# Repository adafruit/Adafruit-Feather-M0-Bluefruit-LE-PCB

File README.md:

## Adafruit Feather M0 Bluefruit LE PCB
<a href="http://www.adafruit.com/products/2995"><br/>
Click here to purchase one from the Adafruit shop</a>

This is the Adafruit Feather M0 Bluefruit LE - our take on an 'all-in-one' Arduino-compatible + Bluetooth Low Energy with built in USB and battery charging. It's an Adafruit Feather M0 with a BTLE module, ready to rock! We have other boards in the Feather family, check'em out here.

Bluetooth Low Energy is a hot, low-power, 2.4GHz spectrum wireless protocol. In particular, it's the only wireless protocol that you can use with iOS without needing special certification, and it's supported by all modern smart phones. This makes it excellent for use in portable projects that will make use of an iOS or Android phone or tablet. It also is supported in Mac OS X and Windows 8+.

At the Feather M0's heart is an ATSAMD21G18 ARM Cortex M0 processor, clocked at 48 MHz and at 3.3V logic, the same one used in the new Arduino Zero. This chip has a whopping 256K of FLASH (8x more than the Atmega328 or 32u4) and 32K of RAM (16x as much)! This chip comes with built in USB so it has USB-to-Serial program & debug capability built in with no need for an FTDI-like chip.

PCB files for the Adafruit Feather M0 Bluefruit LE PCB. The format is EagleCAD schematic and board layout
- https://www.adafruit.com/product/2995

### License

Adafruit invests time and resources providing this open source design, please support Adafruit and open-source hardware by purchasing products from [Adafruit](https://www.adafruit.com)!

All text above must be included in any redistribution

Designed by Limor Fried/Ladyada for Adafruit Industries.
Creative Commons Attribution/Share-Alike, all text above must be included in any redistribution. 
See license.txt for additional information.

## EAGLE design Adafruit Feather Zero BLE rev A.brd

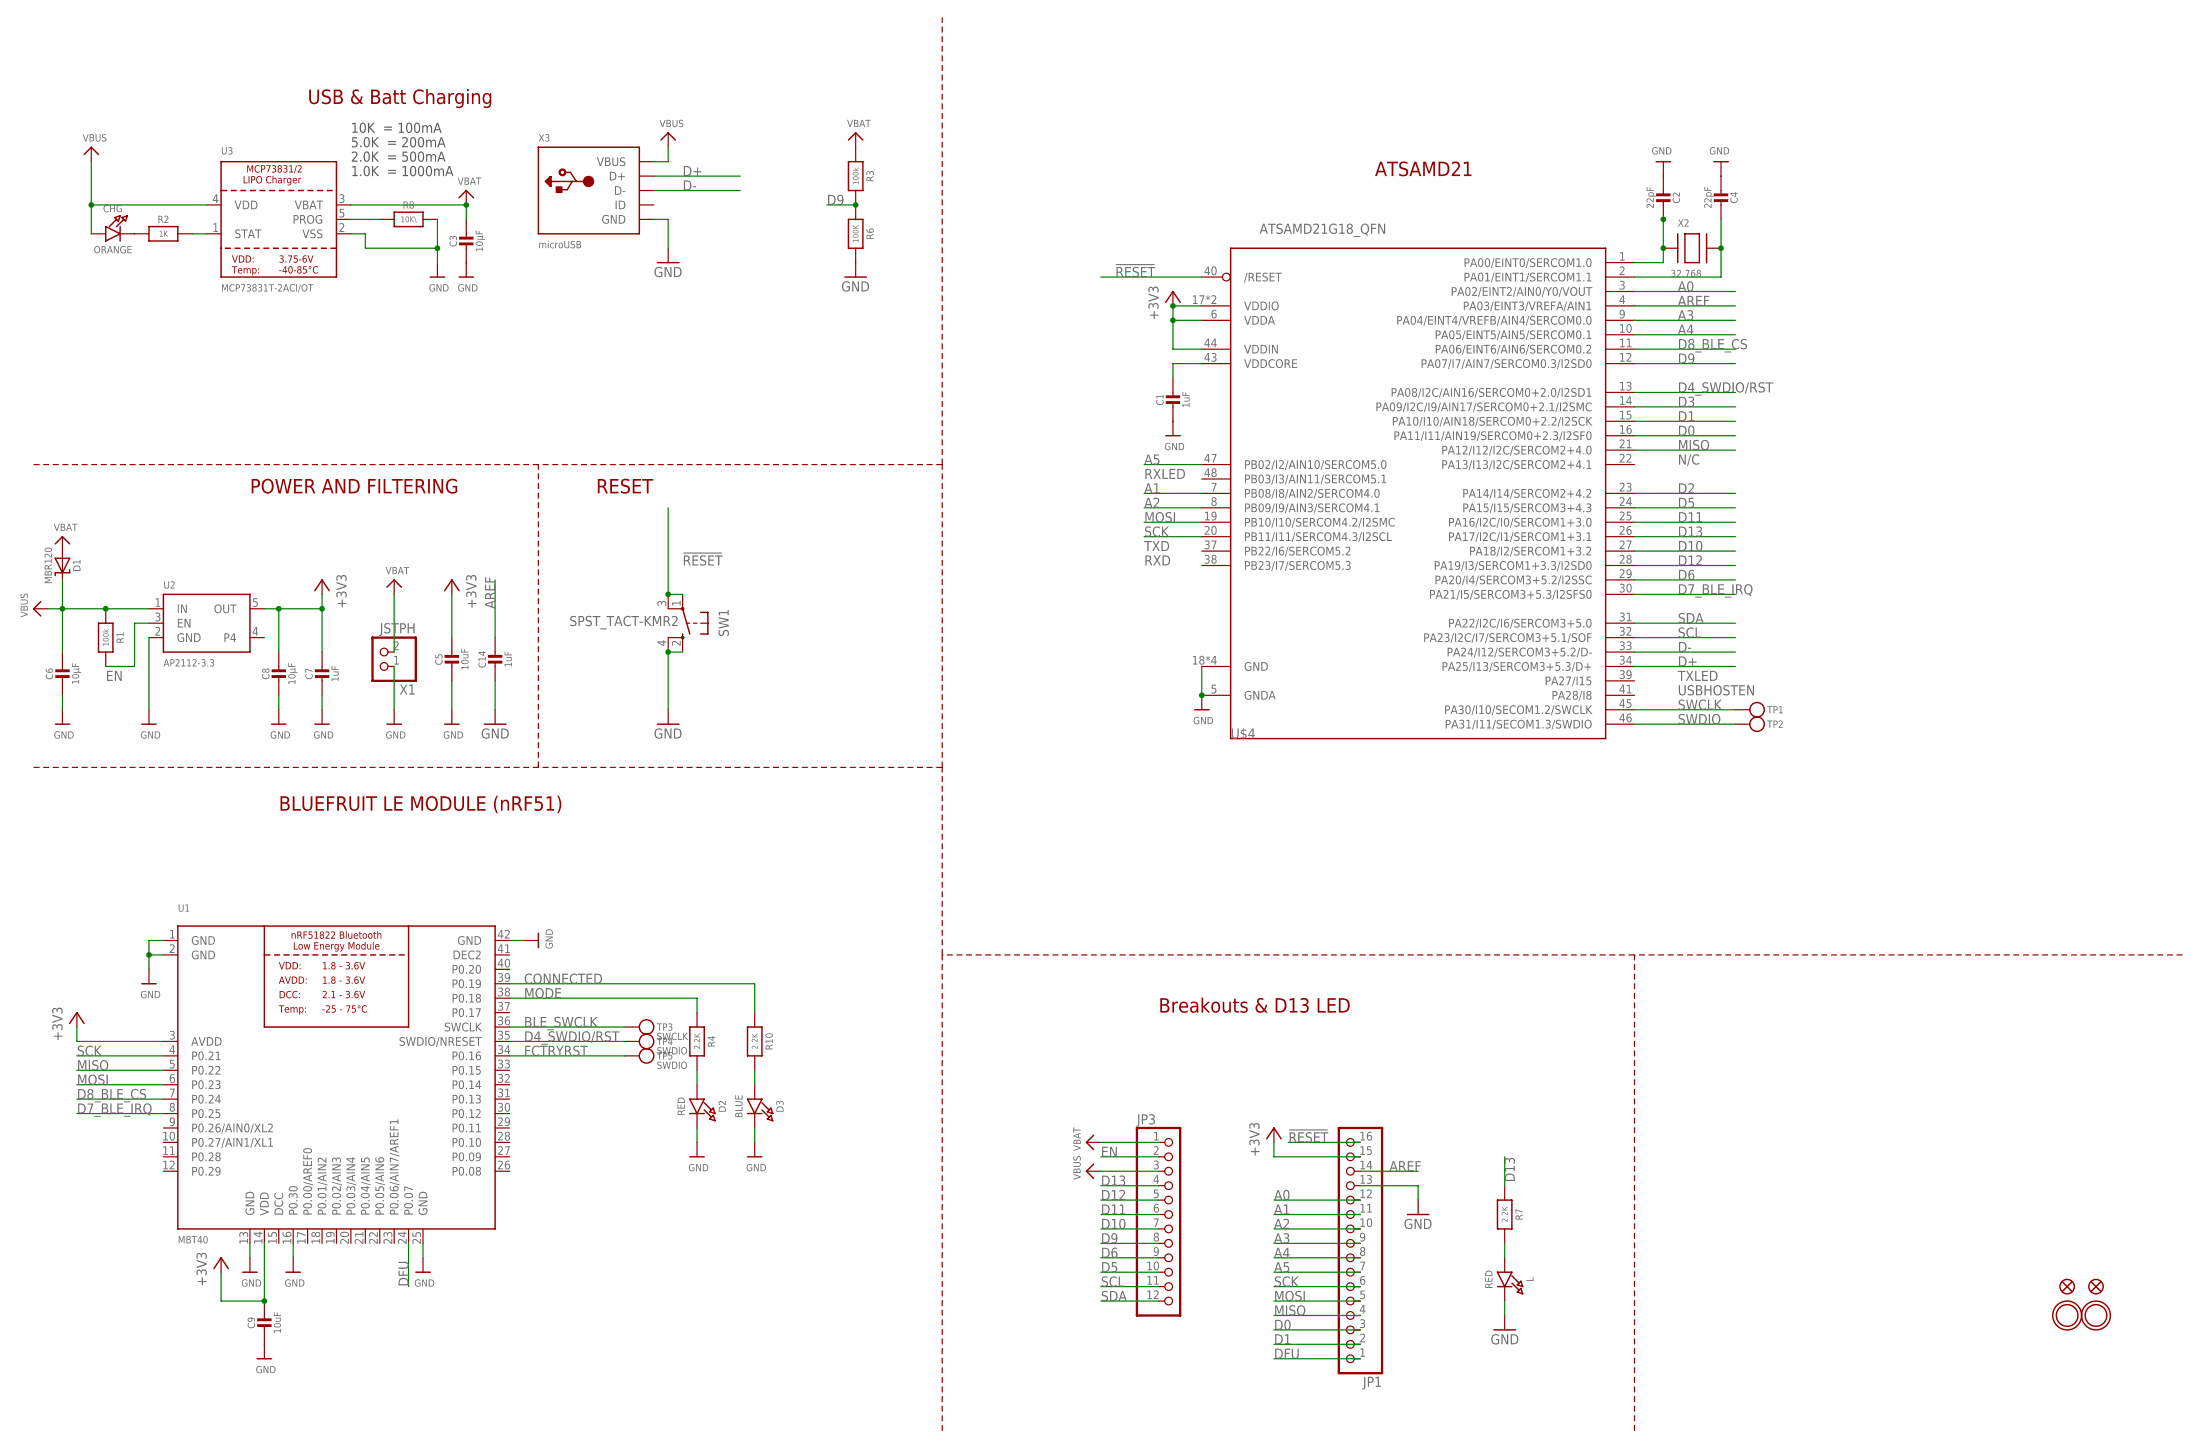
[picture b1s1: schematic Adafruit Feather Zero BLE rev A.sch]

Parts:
C1, C7, C14: 1uF; 0603-NO
C2, C4: 22pF; 0603-NO
C3, C6, C8: 10µF; 0805-NO
C5, C9: 10uF; 0805-NO
CHG: ORANGE; CHIPLED_0805_NOOUTLINE
D1: MBR120; SOD-123
D2: RED; CHIPLED_0805_NOOUTLINE
D3: BLUE; CHIPLED_0805_NOOUTLINE
JP1: HEADER-1X16ROUND; 1X16_ROUND
JP3: HEADER-1X12; 1X12_ROUND
L: RED; CHIPLED_0805_NOOUTLINE
R1, R3: 100k; 0603-NO
R2: 1K; 0603-NO
R4, R7, R10: 2.2K; 0603-NO
R6: 100K; 0603-NO
R8: 10K\; 0603-NO
SW1: SPST_TACT-KMR2; KMR2
TP1, TP2: TESTPOINTROUND1.5MM; TESTPOINT_ROUND_1.5MM
TP3: SWCLK; PAD-1.5X2.0
TP4, TP5: SWDIO; PAD-1.5X2.0
U1: MBT40; BLE_MODULE_RAYTAC_MDBT40
U2: AP2112-3.3; SOT23-5
U3: MCP73831T-2ACI/OT; SOT23-5
U$4: ATSAMD21G18_QFN; TQFN48_7MM
U$31, U$32: MOUNTINGHOLE2.5; MOUNTINGHOLE_2.5_PLATED
U$34, U$35: FIDUCIAL""; FIDUCIAL_1MM
X1: JSTPH; JSTPH2
X2: 32.768; XTAL3215
X3: microUSB; 4UCONN_20329_V2

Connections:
!RESET: JP1.16, SW1.1, SW1.3 (P1), U$4.40 (/RESET)
+3V3: C5.1, C7.1, C8.1, C9.1, JP1.15, U1.3 (AVDD), U1.14 (VDD), U2.5 (OUT), U$4.6 (VDDA), U$4.17 (VDDIO), U$4.36 (VDDIO), U$4.44 (VDDIN)
A0: JP1.12, U$4.3 (PA02/EINT2/AIN0/Y0/VOUT)
A1: JP1.11, U$4.7 (PB08/I8/AIN2/SERCOM4.0)
A2: JP1.10, U$4.8 (PB09/I9/AIN3/SERCOM4.1)
A3: JP1.9, U$4.9 (PA04/EINT4/VREFB/AIN4/SERCOM0.0)
A4: JP1.8, U$4.10 (PA05/EINT5/AIN5/SERCOM0.1)
A5: JP1.7, U$4.47 (PB02/I2/AIN10/SERCOM5.0)
AREF: C14.1, JP1.14, U$4.4 (PA03/EINT3/VREFA/AIN1)
BLE_SWCLK: TP3.P$1, U1.36 (SWCLK)
CONNECTED: R10.1, U1.39 (P0.19)
D0: JP1.3, U$4.16 (PA11/I11/AIN19/SERCOM0+2.3/I2SF0)
D1: JP1.2, U$4.15 (PA10/I10/AIN18/SERCOM0+2.2/I2SCK)
D2: U$4.23 (PA14/I14/SERCOM2+4.2)
D3: U$4.14 (PA09/I2C/I9/AIN17/SERCOM0+2.1/I2SMC)
D4_SWDIO/RST: TP4.P$1, U1.35 (SWDIO/NRESET), U$4.13 (PA08/I2C/AIN16/SERCOM0+2.0/I2SD1)
D5: JP3.10, U$4.24 (PA15/I15/SERCOM3+4.3)
D6: JP3.9, U$4.29 (PA20/I4/SERCOM3+5.2/I2SSC)
D7_BLE_IRQ: U1.8 (P0.25), U$4.30 (PA21/I5/SERCOM3+5.3/I2SFS0)
D8_BLE_CS: U1.7 (P0.24), U$4.11 (PA06/EINT6/AIN6/SERCOM0.2)
D9: JP3.8, R3.2, R6.1, U$4.12 (PA07/I7/AIN7/SERCOM0.3/I2SD0)
D10: JP3.7, U$4.27 (PA18/I2/SERCOM1+3.2)
D11: JP3.6, U$4.25 (PA16/I2C/I0/SERCOM1+3.0)
D12: JP3.5, U$4.28 (PA19/I3/SERCOM1+3.3/I2SD0)
D13: JP3.4, R7.1, U$4.26 (PA17/I2C/I1/SERCOM1+3.1)
D+: U$4.34 (PA25/I13/SERCOM3+5.3/D+), X3.D+
D-: U$4.33 (PA24/I12/SERCOM3+5.2/D-), X3.D-
DCC: U1.15 (DCC)
DEC2: U1.41 (DEC2)
DFU: JP1.1, U1.24 (P0.07)
EN: JP3.2, R1.2, U2.3 (EN)
FCTRYRST: TP5.P$1, U1.34 (P0.16)
GND: C1.2, C2.2, C3.2, C4.2, C5.2, C6.2, C7.2, C8.2, C9.2, C14.2, D2.C, D3.C, JP1.13, L.C, R6.2, R8.2, SW1.2 (S), SW1.4 (S1), U1.1 (GND), U1.2 (GND), U1.13 (GND), U1.16 (P0.30), U1.25 (GND), U1.42 (GND), U2.2 (GND), U3.2 (VSS), U$4.5 (GNDA), U$4.18 (GND), U$4.35 (GND), U$4.42 (GND), U$4.THERMAL (GND), X1.1, X3.BASE@1 (GND), X3.BASE@2 (GND), X3.GND, X3.SPRT@1 (GND), X3.SPRT@2 (GND), X3.SPRT@3 (GND), X3.SPRT@4 (GND)
MISO: JP1.4, U1.5 (P0.22), U$4.21 (PA12/I12/I2C/SERCOM2+4.0)
MODE: R4.1, U1.38 (P0.18)
MOSI: JP1.5, U1.6 (P0.23), U$4.19 (PB10/I10/SERCOM4.2/I2SMC)
unnamed: CHG.C, R2.1
unnamed: L.A, R7.2
unnamed: R2.2, U3.1 (STAT)
unnamed: R8.1, U3.5 (PROG)
unnamed: C2.1, U$4.1 (PA00/EINT0/SERCOM1.0), X2.P$1
unnamed: D2.A, R4.2
unnamed: C4.1, U$4.2 (PA01/EINT1/SERCOM1.1), X2.P$2
unnamed: D3.A, R10.2
SCK: JP1.6, U1.4 (P0.21), U$4.20 (PB11/I11/SERCOM4.3/I2SCL)
SCL: JP3.11, U$4.32 (PA23/I2C/I7/SERCOM3+5.1/SOF)
SDA: JP3.12, U$4.31 (PA22/I2C/I6/SERCOM3+5.0)
SWCLK: TP1.P$1, U$4.45 (PA30/I10/SECOM1.2/SWCLK)
SWDIO: TP2.P$1, U$4.46 (PA31/I11/SECOM1.3/SWDIO)
VBAT: C3.1, D1.A, JP3.1, R3.1, U3.3 (VBAT), X1.2
VBUS: C6.1, CHG.A, D1.C, JP3.3, R1.1, U2.1 (IN), U3.4 (VDD), X3.VBUS
VDDCORE: C1.1, U$4.43 (VDDCORE)

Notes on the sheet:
POWER AND FILTERING
RESET
10K = 100mA
5.0K = 200mA
2.0K = 500mA
1.0K = 1000mA
N/C
TXLED
USBHOSTEN
RXLED
TXD
RXD
BLUEFRUIT LE MODULE (nRF51)
ATSAMD21
USB & Batt Charging
Breakouts & D13 LED

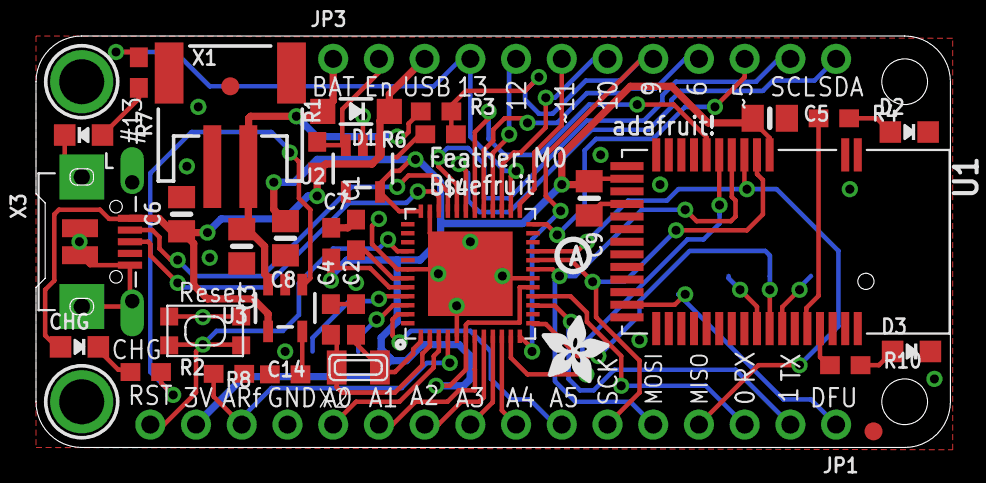
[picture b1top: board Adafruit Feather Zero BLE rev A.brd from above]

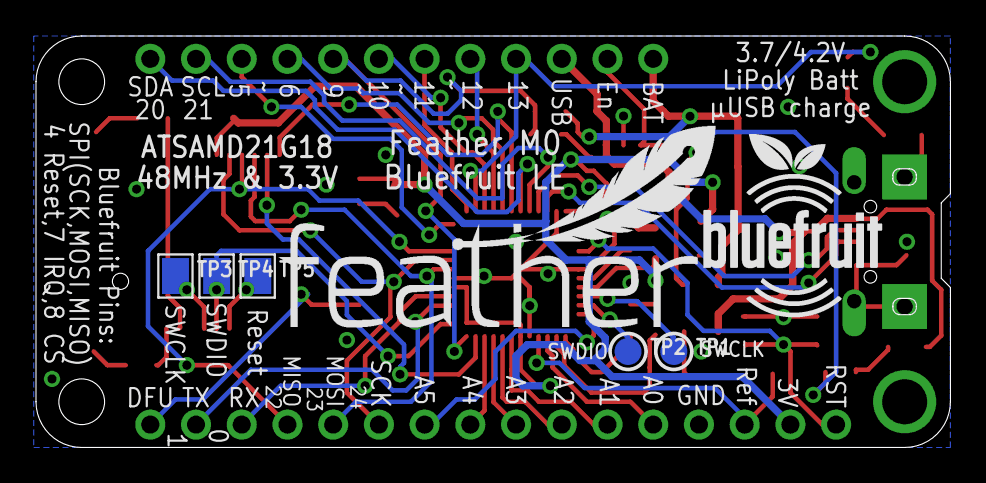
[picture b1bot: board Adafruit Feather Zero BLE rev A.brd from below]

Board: 2 copper layers, 50.8 x 22.9 mm, 46 parts (7 on the bottom side), 48 nets.

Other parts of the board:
U$7: ADAFRUIT_3.5MM
U$9: FEATHERLOGO
U$25: PCBFEAT-REV-040
U$26: BLUEFRUITLOGO_100MM

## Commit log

2016-05-17 init!
2022-04-19 Added PrettyPins

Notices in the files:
parts and their libraries:
microbuilder: This work is placed in the public domain, and may be freely used for commercial and non-commercial work with the following conditions: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
